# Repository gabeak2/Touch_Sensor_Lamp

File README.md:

# Touch_Sensor_Lamp
A small PCB with a capacitive touch sensor IC and 2 1W LEDs.  I use them to embed in 3d-printed lithophane lamps, see 

https://www.youtube.com/shorts/fURaeRKdgpU

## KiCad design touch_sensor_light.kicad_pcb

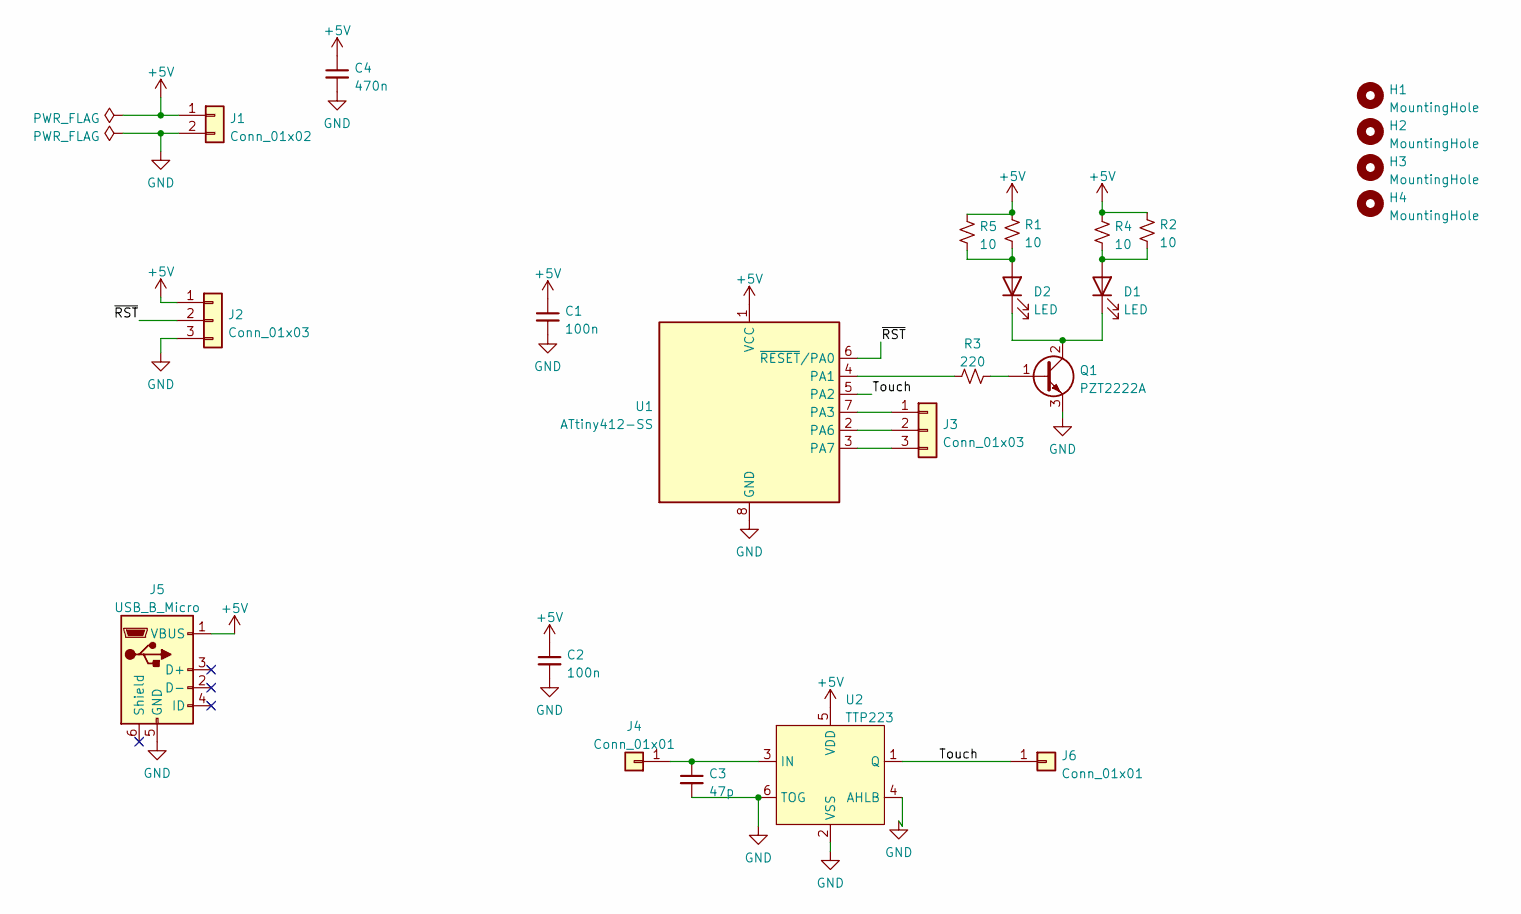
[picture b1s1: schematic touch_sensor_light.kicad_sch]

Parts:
C1, C2: 100n; C_0805_2012Metric; JLCPCB PN C49678
C3: 47p; C_0805_2012Metric; JLCPCB PN C14857
C4: 470n; C_0805_2012Metric; JLCPCB PN C13967
D1, D2: LED; LED_1W_3W_R8
H1, H2, H3, H4: MountingHole; MountingHole_2.2mm_M2
J1: Conn_01x02; PinSocket_1x02_P2.54mm_Vertical
J2, J3: Conn_01x03; PinSocket_1x03_P2.54mm_Vertical
J4, J6: Conn_01x01; PinSocket_1x01_P2.54mm_Vertical
J5: USB_B_Micro; USB_Micro-B_Molex-105017-0001; JLCPCB PN C404969
Q1: PZT2222A; SOT-223-3_TabPin2
R1, R2, R4, R5: 10; R_1206_3216Metric; JLCPCB PN C17903
R3: 220; R_0805_2012Metric; JLCPCB PN C17557
U1: ATtiny412-SS; SOIC-8_3.9x4.9mm_P1.27mm
U2: TTP223; SOT-23-6; JLCPCB PN C80803

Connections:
+5V: C1.1, C2.1, C4.1, J1.1, J2.1, J5.1 (VBUS), R1.1, R2.1, R4.1, R5.1, U1.1 (VCC), U2.5 (VDD)
/Touch: J6.1, U1.5 (PA2), U2.1 (Q)
/~RST: J2.2, U1.6 (~RESET/PA0)
GND: C1.2, C2.2, C3.2, C4.2, J1.2, J2.3, J5.5 (GND), Q1.3 (E), U1.8 (GND), U2.2 (VSS), U2.4 (AHLB), U2.6 (TOG)
unnamed: C3.1, J4.1, U2.3 (IN)
unnamed: D1.1 (K), D2.1 (K), Q1.2 (C)
unnamed: D1.2 (A), R2.2, R4.2
unnamed: D2.2 (A), R1.2, R5.2
unnamed: J3.1, U1.7 (PA3)
unnamed: J3.2, U1.2 (PA6)
unnamed: J3.3, U1.3 (PA7)
unnamed: Q1.1 (B), R3.2
unnamed: R3.1, U1.4 (PA1)

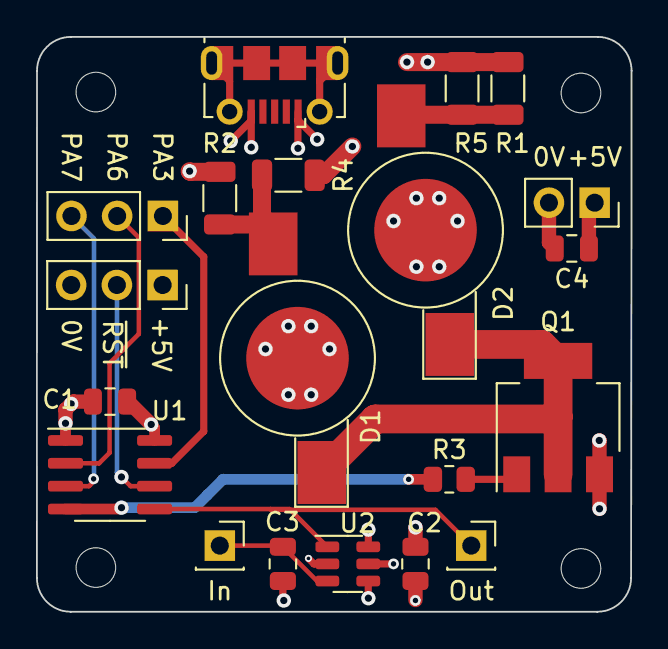
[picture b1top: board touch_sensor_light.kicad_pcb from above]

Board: 4 copper layers, 33.0 x 31.9 mm, 24 parts (0 on the bottom side), 13 nets.
